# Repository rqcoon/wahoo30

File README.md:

# Wahoo!
---
a totally not gherkin based off the CH552T microcontroller and [FAK firmware](https://github.com/semickolon/fak)

all of the files needed to produce the pcb should be here.

for compiling and flashing the firmware just copy the provided `.ncl` files into the ncl/ directory when following the FAK flashing guide (available [here](https://github.com/semickolon/fak/blob/main/README.md))

big shout outs to semickolon and apfel from the FAK discord!

---
TODO: case (I intend on making a 3d printable case similar to pohjolaworks' [Umo](https://github.com/pohjolaworks/Umo))

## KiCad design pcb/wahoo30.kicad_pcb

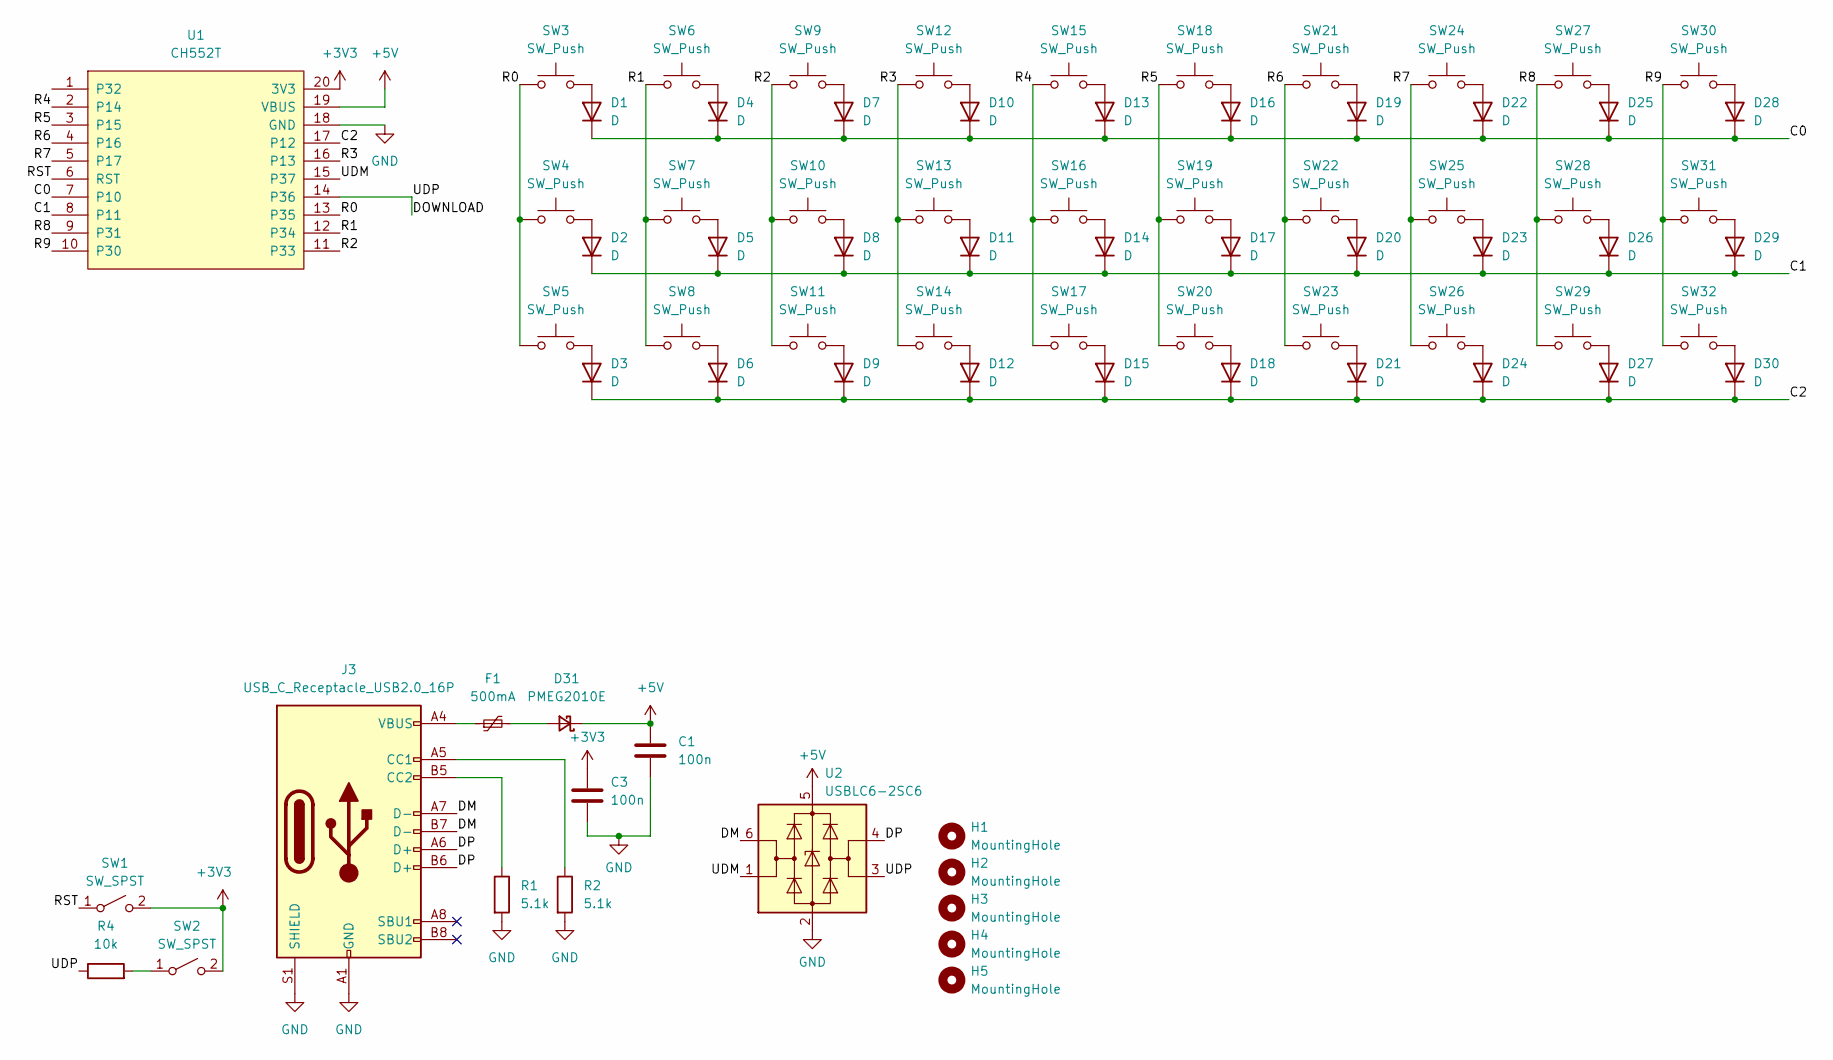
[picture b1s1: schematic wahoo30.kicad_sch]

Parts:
C1, C3: 100n; D_0805_2012Metric_Pad1.15x1.40mm_HandSolder
D1, D2, D3, D4, D5, D6, D7, D8, D9, D10, D11, D12, D13, D14, D15, D16, D17, D18, D19, D20, D21, D22, D23, D24, D25, D26, D27, D28, D29, D30: D; D_0805_2012Metric_Pad1.15x1.40mm_HandSolder
D31: PMEG2010E; D_0805_2012Metric_Pad1.15x1.40mm_HandSolder
F1: 500mA; Fuse_0805_2012Metric_Pad1.15x1.40mm_HandSolder
H1, H2, H3, H4, H5: MountingHole; MountingHole_2.2mm_M2_ISO7380
J3: USB_C_Receptacle_USB2.0_16P; USB_C_Receptacle_HRO_TYPE-C-31-M-12
R1, R2: 5.1k; R_0805_2012Metric_Pad1.20x1.40mm_HandSolder
R4: 10k; R_0805_2012Metric_Pad1.20x1.40mm_HandSolder
SW1, SW2: SW_SPST; PinHeader_1x02_P2.00mm_Vertical
SW3, SW4, SW5, SW6, SW7, SW8, SW9, SW10, SW11, SW12, SW13, SW14, SW15, SW16, SW17, SW18, SW19, SW20, SW21, SW22, SW23, SW24, SW25, SW26, SW27, SW28, SW29, SW30, SW31, SW32: SW_Push; SW_Cherry_MX_PCB_1.00u
U1: CH552T; TSSOP-20-1EP_4.4x6.5mm_P0.65mm_EP2.15x3.35mm
U2: USBLC6-2SC6; SOT-23-6

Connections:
+3V3: C3.1, SW1.2 (B), SW2.2 (B), U1.20 (3V3)
+5V: C1.1, D31.1 (K), U1.19 (VBUS), U2.5 (VBUS)
/C0: D1.1 (K), D4.1 (K), D7.1 (K), D10.1 (K), D13.1 (K), D16.1 (K), D19.1 (K), D22.1 (K), D25.1 (K), D28.1 (K), U1.7 (P10)
/C1: D2.1 (K), D5.1 (K), D8.1 (K), D11.1 (K), D14.1 (K), D17.1 (K), D20.1 (K), D23.1 (K), D26.1 (K), D29.1 (K), U1.8 (P11)
/C2: D3.1 (K), D6.1 (K), D9.1 (K), D12.1 (K), D15.1 (K), D18.1 (K), D21.1 (K), D24.1 (K), D27.1 (K), D30.1 (K), U1.17 (P12)
/DM: J3.A7 (D-), J3.B7 (D-), U2.6 (I/O1)
/DOWNLOAD: R4.1, U1.14 (P36), U2.3 (I/O2)
/DP: J3.A6 (D+), J3.B6 (D+), U2.4 (I/O2)
/R0: SW3.1, SW4.1, SW5.1, U1.13 (P35)
/R1: SW6.1, SW7.1, SW8.1, U1.12 (P34)
/R2: SW9.1, SW10.1, SW11.1, U1.11 (P33)
/R3: SW12.1, SW13.1, SW14.1, U1.16 (P13)
/R4: SW15.1, SW16.1, SW17.1, U1.2 (P14)
/R5: SW18.1, SW19.1, SW20.1, U1.3 (P15)
/R6: SW21.1, SW22.1, SW23.1, U1.4 (P16)
/R7: SW24.1, SW25.1, SW26.1, U1.5 (P17)
/R8: SW27.1, SW28.1, SW29.1, U1.9 (P31)
/R9: SW30.1, SW31.1, SW32.1, U1.10 (P30)
/RST: SW1.1 (A), U1.6 (RST)
/UDM: U1.15 (P37), U2.1 (I/O1)
GND: C1.2, C3.2, J3.A1 (GND), J3.A12 (GND), J3.B1 (GND), J3.B12 (GND), J3.S1 (SHIELD), R1.2, R2.2, U1.18 (GND), U2.2 (GND)
unnamed: D1.2 (A), SW3.2
unnamed: D2.2 (A), SW4.2
unnamed: D3.2 (A), SW5.2
unnamed: D4.2 (A), SW6.2
unnamed: D5.2 (A), SW7.2
unnamed: D6.2 (A), SW8.2
unnamed: D7.2 (A), SW9.2
unnamed: D8.2 (A), SW10.2
unnamed: D9.2 (A), SW11.2
unnamed: D10.2 (A), SW12.2
unnamed: D11.2 (A), SW13.2
unnamed: D12.2 (A), SW14.2
unnamed: D13.2 (A), SW15.2
unnamed: D14.2 (A), SW16.2
unnamed: D15.2 (A), SW17.2
unnamed: D16.2 (A), SW18.2
unnamed: D17.2 (A), SW19.2
unnamed: D18.2 (A), SW20.2
unnamed: D19.2 (A), SW21.2
unnamed: D20.2 (A), SW22.2
unnamed: D21.2 (A), SW23.2
unnamed: D22.2 (A), SW24.2
unnamed: D23.2 (A), SW25.2
unnamed: D24.2 (A), SW26.2
unnamed: D25.2 (A), SW27.2
unnamed: D26.2 (A), SW28.2
unnamed: D27.2 (A), SW29.2
unnamed: D28.2 (A), SW30.2
unnamed: D29.2 (A), SW31.2
unnamed: D30.2 (A), SW32.2
unnamed: D31.2 (A), F1.2
unnamed: F1.1, J3.A4 (VBUS), J3.A9 (VBUS), J3.B4 (VBUS), J3.B9 (VBUS)
unnamed: J3.A5 (CC1), R2.1
unnamed: J3.B5 (CC2), R1.1
unnamed: R4.2, SW2.1 (A)

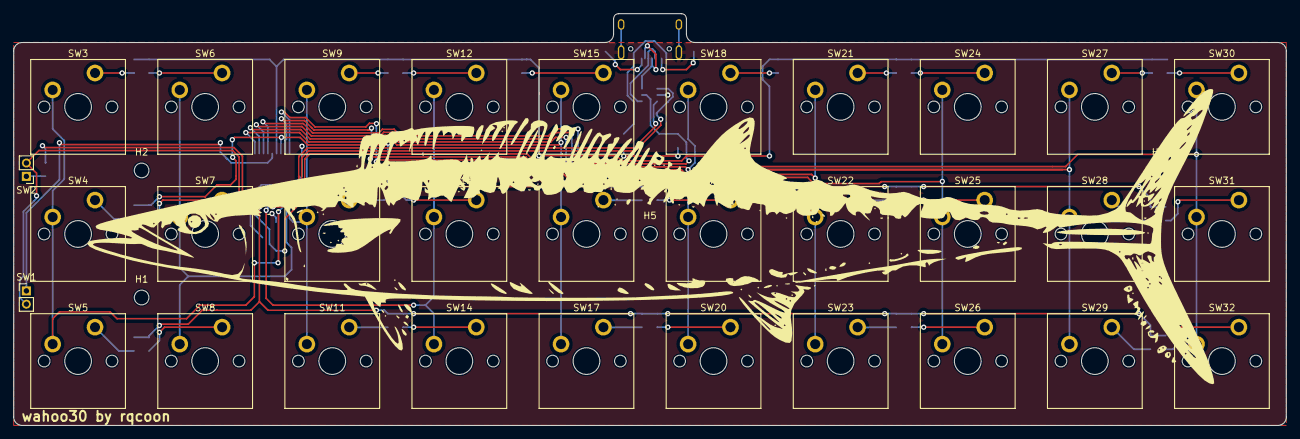
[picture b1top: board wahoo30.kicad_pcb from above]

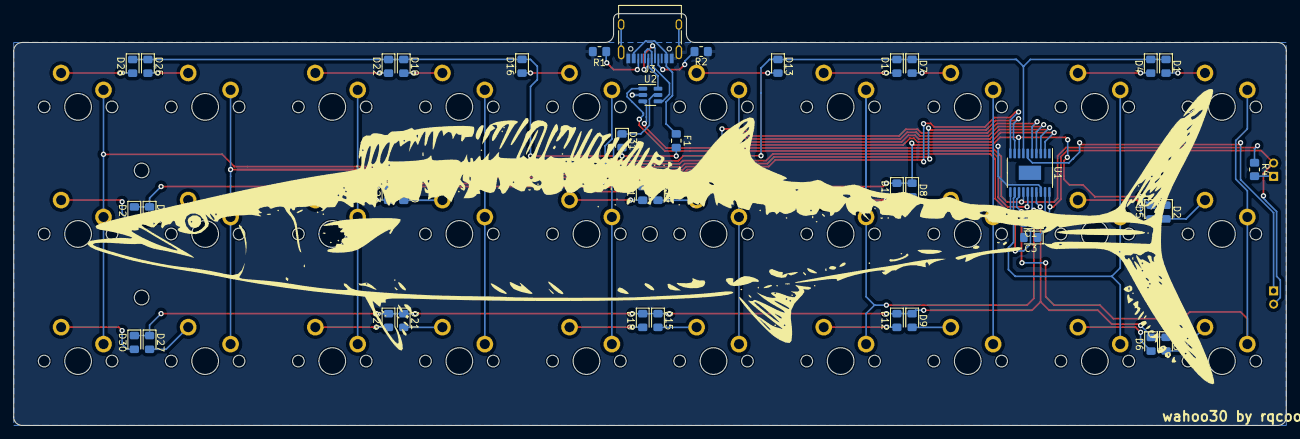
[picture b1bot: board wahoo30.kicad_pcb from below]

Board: 2 copper layers, 190.8 x 61.7 mm, 77 parts (40 on the bottom side), 56 nets.

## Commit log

2024-03-22 ignore backups
2024-03-22 gitfun
2024-03-22 fix README and LICENSE
2024-03-22 readme.md
